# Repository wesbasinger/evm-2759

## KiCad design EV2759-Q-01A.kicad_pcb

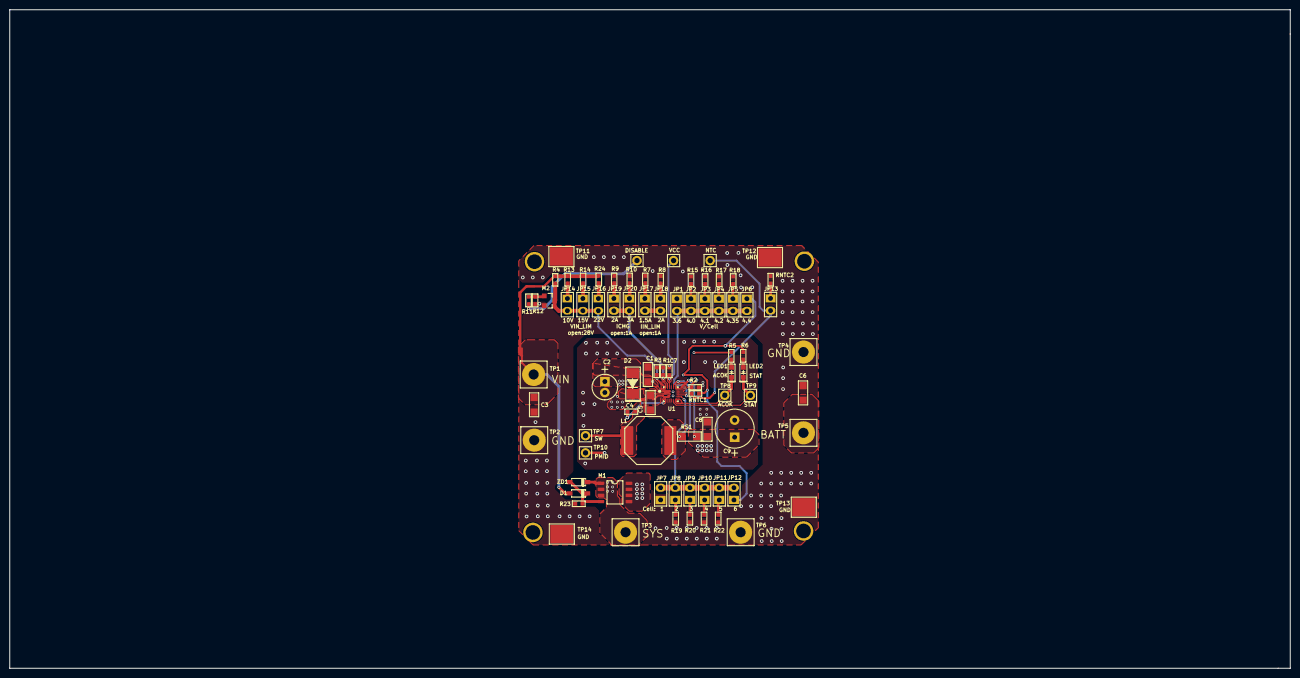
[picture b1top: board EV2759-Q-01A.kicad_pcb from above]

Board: 4 copper layers, 266.7 x 137.2 mm, 82 parts (0 on the bottom side), 37 nets.

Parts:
C1, C3, C5, C6, C8: CAP/1206
C2: CAP/ELECT/DIP/OD5.3P2.0
C4, C7: CAP/0603
C9: CAP/ELECT/DIP/OD8.0P3.5
D1: 1N4148W; DIODES/SOD-123
D2: B330B; DIODES/SMA
DISABLE: NTC; CONN/TP
JP1, JP2, JP3, JP4, JP5, JP6, JP7, JP8, JP9, JP10, JP11, JP12, JP13, JP17, JP18, JP19, JP20: JUMPER/2P/DIP/2.54MM/C; CONN/DIP/2PIN/2.54MM/A
JP14: 10V; CONN/DIP/2PIN/2.54MM/A
JP15: 15V; CONN/DIP/2PIN/2.54MM/A
JP16: 22V; CONN/DIP/2PIN/2.54MM/A
L1: INDUCTOR; 2759-744066100
LED1: ACOK; LED/SMD/0805
LED2: STAT; LED/SMD/0805
M1: AM4417P; MOS/SO8
M2: 2N7002; MOS/SOT23
NTC: NTC; CONN/TP
R1, R2, R3, R4, R5, R6, R7, R8, R9, R10, R11, R12, R13, R14, R15, R16, R17, R18, R19, R20, R21, R22, R23, R24: RES/0603
RNTC1, RNTC2: RES/0603
RS1: RES/1206
TP1: VIN; CONN/2MM
TP2, TP4, TP6: GND; CONN/2MM
TP3: SYS; CONN/2MM
TP5: BATT; CONN/2MM
TP7: SW; CONN/TP
TP8: ACOK; CONN/TP
TP9: STAT; CONN/TP
TP10: PMID; CONN/TP
TP11, TP12, TP13, TP14: GND; TP_GND
U1: MP2759GQ; PCBComponent_1
VCC: NTC; CONN/TP
ZD1: DIODES/ZENER/SOD-123; DIODES/SOD-123

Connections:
ACOK: LED1.1, TP8.1, U1.9
BATT: C6.2, C8.2, C9.1, M1.5, M1.6, M1.7, M1.8, RS1.2, TP5.1, U1.14
CELL: JP7.2, JP8.2, JP9.2, JP10.2, JP11.2, JP12.2, U1.10
DISABLE: DISABLE.1, R11.2
GND: C1.1, C2.2, C3.1, C5.2, C6.1, C7.2, C8.1, C9.2, JP1.1, JP7.1, M2.2, R1.2, R2.2, R3.2, R7.2, R8.2, R9.2, R10.2, R12.1, R15.2, R16.2, R17.2, R18.2, R19.2, R20.2, R21.2, R22.2, R23.1, RNTC2.2, TP2.1, TP4.1, TP6.1, TP11.1, TP12.1, TP13.1, TP14.1, U1.5, U1.6, U1.7, U1.16
ILIM: JP17.2, JP18.2, R2.1, U1.13
ISET: JP19.2, JP20.2, R1.1, U1.18
NTC: JP13.2, NTC.1, RNTC1.2, U1.12
NetC4_2: C4.2, U1.4
NetD1_2: D1.2, M1.4, R23.2, ZD1.1
NetJP2_1: JP2.1, R15.1
NetJP3_1: JP3.1, R16.1
NetJP4_1: JP4.1, R17.1
NetJP5_1: JP5.1, R18.1
NetJP8_1: JP8.1, R19.1
NetJP9_1: JP9.1, R20.1
NetJP10_1: JP10.1, R21.1
NetJP11_1: JP11.1, R22.1
NetJP13_1: JP13.1, RNTC2.1
NetJP14_1: JP14.1, R13.2
NetJP15_1: JP15.1, R14.2
NetJP16_1: JP16.1, R24.2
NetJP17_1: JP17.1, R7.1
NetJP18_1: JP18.1, R8.1
NetJP19_1: JP19.1, R9.1
NetJP20_1: JP20.1, R10.1
NetL1_2: L1.2, RS1.1, U1.15
NetLED1_2: LED1.2, R5.2
NetLED2_2: LED2.2, R6.1
NetM2_1: M2.1, R11.1, R12.2
PMID: C5.1, D2.2, M1.1, M1.2, M1.3, TP3.1, TP10.1, U1.2, ZD1.2
STAT: LED2.1, TP9.1, U1.8
SW: C4.1, L1.1, TP7.1, U1.3
VB: JP1.2, JP2.2, JP3.2, JP4.2, JP5.2, JP6.2, U1.11
VCC: C7.1, JP6.1, JP12.1, R6.2, RNTC1.1, U1.17, VCC.1
VIN: C1.2, C2.1, C3.2, D1.1, D2.1, R4.2, R5.1, R13.1, R14.1, R24.1, TP1.1, U1.1
VLIM: JP14.2, JP15.2, JP16.2, M2.3, R3.1, R4.1, U1.19

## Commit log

2023-11-02 Switched main chip to supported model.
